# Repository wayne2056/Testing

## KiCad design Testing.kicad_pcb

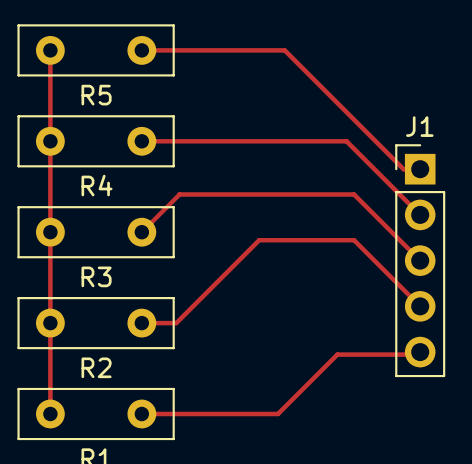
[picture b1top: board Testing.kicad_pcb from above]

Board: 2 copper layers, 6 parts (0 on the bottom side), 6 nets.

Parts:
J1: Conn_01x05_Male; PinHeader_1x05_P2.54mm_Vertical
R1, R2, R3, R4, R5: R; R_Box_L8.4mm_W2.5mm_P5.08mm

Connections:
/NET1: J1.5, R1.1
/NET2: J1.4, R2.1
/NET3: J1.3, R3.1
/NET4: J1.2, R4.1
/NET5: J1.1, R5.1
GND: R1.2, R2.2, R3.2, R4.2, R5.2

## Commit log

2022-08-04 First Commit.
2022-08-04 Added a Capacitor
2022-08-04 Added 2nd Capacitor.
2022-08-04 Added a Diode.
2022-08-05 Update Testing.kicad_sch
    Change NET LABEL 5 to 9999
